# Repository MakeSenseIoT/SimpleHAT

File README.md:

## MakeSenseIoT SimpleHAT

<br/>

PCB files for the SimpleHAT by MakeSenseIoT  

Format is EagleCAD schematic and board layout

### Hardware

The SimpleHAT is a Raspberry Pi Zero W HAT with multiple functionalities. 
It can operate as a standalone unit or as a part of more complex system, for example
Solar Powered IoT camera. 
The SimpleHAT hardware includes:

* Circutry for powering ON/OFF Raspberry Pi using external signal 
* Placeholder for Raspberry Pi Camera module
* Placeholder for 0.91" OLED display module
* Placeholder for 1.3" OLED display module
* Placeholder for UART to USB converter
* Placeholder for I2C (QWIIC)

Note: Due to physical limitation, not all hardware options can be used togrther

### RPI Software
* ON/OFF

For ON/OFF functionality use Pimoroni one-line installer for daemon configuration:

```
curl https://get.pimoroni.com/onoffshim | bash
```
 **IMPORTANT** Do not use pushbutton while using external signal for ON/OF
as it might result in damaging of external driving circuitry. There is no protecting
circuit to prevent it. Use only one ON/OFF source at a time.

* I2C OLEDs
There are multiple online tutorials and example code available online 

* Raspberry Pi Camera UV4L 
There are multiple online tutorials and example code available online. We use UV4L - for installation details
see [UV4L](https://www.linux-projects.org/uv4l/installation/)

## Authors

* **Jan Szymanski** - *Initial work* - [MakeSenseIoT](http://www.makesenseiot.com)

## Acknowledgments

* The OnOff SHIM code by Pimoroni is used
* Inspired by Pimoroni project updated and modified [Pimoroni](https://shop.pimoroni.com/products/onoff-shim)

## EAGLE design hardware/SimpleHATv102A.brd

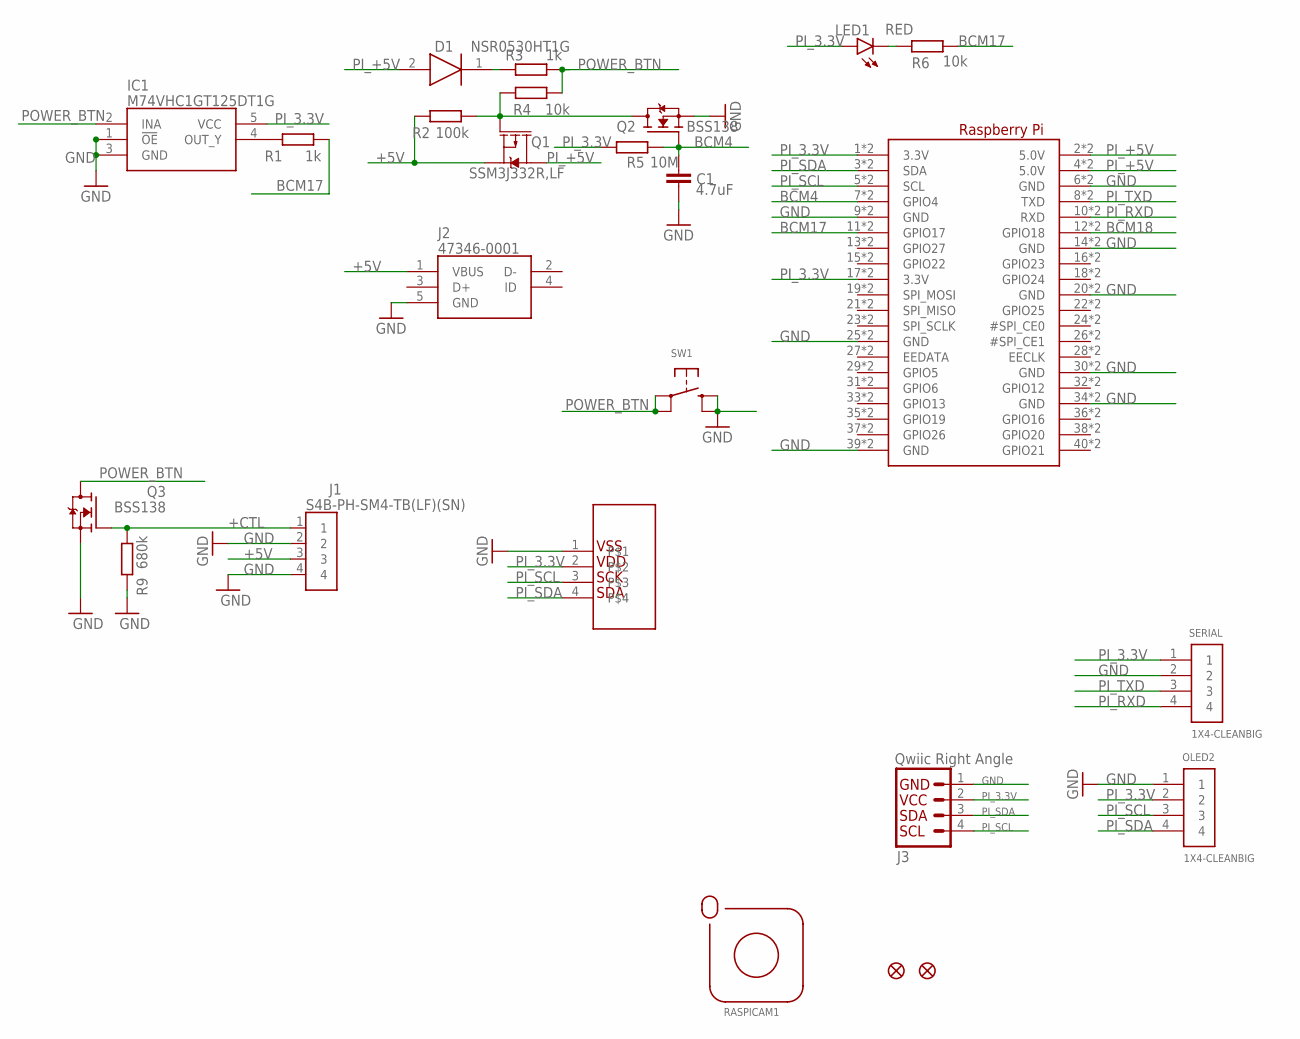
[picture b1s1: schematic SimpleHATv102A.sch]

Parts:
C1: 4.7uF; C0805K
D1: NSR0530HT1G; SOD2512X110N
FD1, FD2: SPARKFUN-AESTHETICS_FIDUCIAL1X2; SPARKFUN-AESTHETICS_FIDUCIAL-1X2
IC1: M74VHC1GT125DT1G; SOT95P275X110-5N
J1: S4B-PH-SM4-TB(LF)(SN); S4B-PH-SM4-TB
J2: 47346-0001
J3: Qwiic Right Angle; SPARKFUN-CONNECTORS_JST04_1MM_RA
LED1: RED; CHIP-LED0603
OLED1: 128X32OLEDMODULE0.96"MODULEPCB; 128X32OLED
OLED2: 1X4-CLEANBIG; 1X04-CLEANBIG
Q1: SSM3J332R,LF; SOT23-3
Q2, Q3: BSS138; SOT23
R1, R3: 1k; R0603
R2: 100k; R0603
R4, R6: 10k; R0603
R5: 10M; R0603
R9: 680k; R0603
RASPICAM1: RASPICAM
RPI1: ADAFRUIT-LORA-RADIO-BONNET-WITH-OLED_MICROBUILDER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; ADAFRUIT-LORA-RADIO-BONNET-WITH-OLED_MICROBUILDER_PI_BONNET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
SERIAL: 1X4-CLEANBIG; 1X04-CLEANBIG
SW1: MICROBUILDER_SWITCH_TACT_SMTKMT0; MICROBUILDER_BTN_KMT0

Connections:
+5V: J1.3, J2.1 (VBUS), Q1.2 (S), R2.2
+CTL: J1.1, Q3.1 (G), R9.1
BCM4: C1.2, Q2.1 (G), R5.1, RPI1.7 (GPIO4), RPI1.S7 (GPIO4)
BCM17: R1.1, R6.2, RPI1.11 (GPIO17), RPI1.S11 (GPIO17)
BCM18: RPI1.12 (GPIO18), RPI1.S12 (GPIO18)
GND: C1.1, IC1.1 (!OE), IC1.3 (GND), J1.2, J1.4, J2.5 (GND), J3.1, OLED1.1, OLED2.1, Q2.2 (S), Q3.2 (S), R9.2, RPI1.6 (GND), RPI1.9 (GND), RPI1.14 (GND), RPI1.20 (GND), RPI1.25 (GND), RPI1.30 (GND), RPI1.34 (GND), RPI1.39 (GND), RPI1.S6 (GND), RPI1.S9 (GND), RPI1.S14 (GND), RPI1.S20 (GND), RPI1.S25 (GND), RPI1.S30 (GND), RPI1.S34 (GND), RPI1.S39 (GND), SERIAL.2, SW1.B (S), SW1.B' (S1)
unnamed: IC1.4 (OUT_Y), R1.2
unnamed: LED1.C, R6.1
unnamed: D1.1 (K), R3.2
unnamed: Q1.1 (G), Q2.3 (D), R2.1, R4.2
PI_3.3V: IC1.5 (VCC), J3.2, LED1.A, OLED1.2, OLED2.2, R5.2, RPI1.1 (3.3V), RPI1.17 (3.3V), RPI1.S1 (3.3V), RPI1.S17 (3.3V), SERIAL.1
PI_+5V: D1.2 (A), Q1.3 (D), RPI1.2 (5.0V), RPI1.4 (5.0V), RPI1.S2 (5.0V), RPI1.S4 (5.0V)
PI_RXD: RPI1.10 (RXD), RPI1.S10 (RXD), SERIAL.4
PI_SCL: J3.4, OLED1.3, OLED2.3, RPI1.5 (SCL), RPI1.S5 (SCL)
PI_SDA: J3.3, OLED1.4, OLED2.4, RPI1.3 (SDA), RPI1.S3 (SDA)
PI_TXD: RPI1.8 (TXD), RPI1.S8 (TXD), SERIAL.3
POWER_BTN: IC1.2 (INA), Q3.3 (D), R3.1, R4.1, SW1.A, SW1.A' (P1)

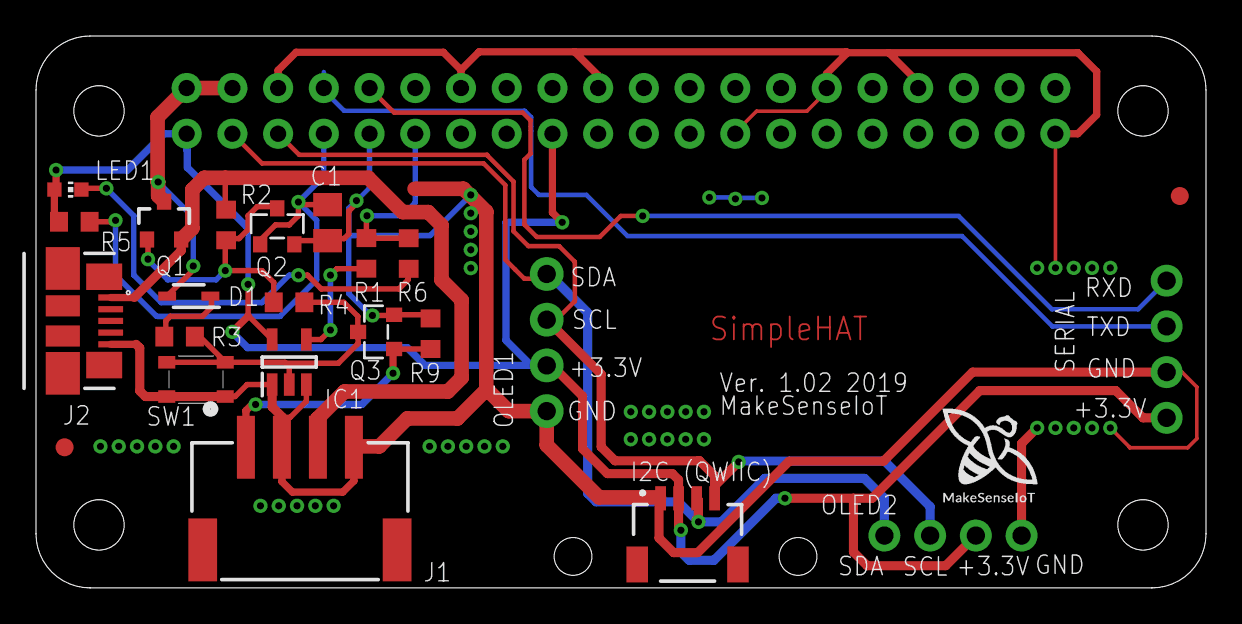
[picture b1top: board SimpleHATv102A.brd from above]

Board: 2 copper layers, 65.0 x 30.7 mm, 25 parts (0 on the bottom side), 17 nets.
